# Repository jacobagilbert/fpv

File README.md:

# Custom FPV Related Software and Hardware
This repository contains various FPV related projects. These are side projects for me, and are free for anyone to use under the MIT license. 
I welcome anyone who would like to help and improve on these!

I will attempt to keep this readme up-to-date and provide all resources I have used.

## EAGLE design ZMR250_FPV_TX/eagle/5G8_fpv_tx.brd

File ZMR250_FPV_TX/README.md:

# Custom FPV Transmitter for ZMR250: The ZTX-23

I suggest you read this entire README prior to building this, it's not that long and there are a few important considerations.

### Version 1.2 Changelog:

The version 1.2 hardware has resolved a few issues and annoyances:

- Addition of LDO to resolve SMPS noise in video
- Input connector is now a 5-pin picoblade to distinguish from the programming header
- Changed footprint for 7343 capacitors
- Switch and LED positions are changed for easier access
- Requires modification of the Pololu module

The remainder of this guide is for v1.2 only.

### Origins:

I had a number of annoyances related to the BOSCAM FPV transmitter I initially purchased for my ZRM250 quadcopter. It was difficult to change frequencies, mounting wasn't ideal, and most of all for whatever reason, it only put out 13.1 dBm (~20mW). I knew I was going to need another one, and I happened to stumble across a [German RC forum post](http://fpv-treff.de/viewtopic.php?f=23&t=5974) where an awesome guy developed a custom transmitter based around the TX5823 200mW 5.8GHz transmitter found in many pre-packaged FPV transmitters. While not exactly what I wanted, it was a great starting point and served as the inspiration for this project.

There are a number of differences from the original work, specifically the ATTiny software and PCB layout are completely new, but they get a ton of credit for all the great stuff in that forum .

### Project Objectives:

This project seeks to produce a 200mW FPV transmitter with the following specifications:

- Easily mounted securely on the ZMR250 frame
- Low profile and does not inhibit use of 6" propellers
- Simple to change channels (no buried DIP switches!)
- Direct 3S/4S power input
- Has frequency agility supporting all current receiver channels (including IRC's new 'RaceBand'!)

### Current System Status Overview:

**ATTiny Firmware:** The current ATTiny firmware has been tested on the hardware platform successfully! There are no known issues with the current software. I have used it many times and overall I am quite pleased. All 5 bands (40 channels total) have been implemented.

**Hardware:** The v2.1 boards are in and have been populated and tested - they function great. These were made through OSHPark and can be ordered [here](https://oshpark.com/shared_projects/h9UIDucG) - $12 for 3 copies. There are several optional components, which are detailed in a subsequent section.

The RF path is a properly dimensioned CPWG transmission line, and while just at the length where it begins to matter (and it's FR4 at 5.8 GHz...), I figured it would be fun to do it properly. The trace is 55 mils wide with 9 mil spacing on 1.6 mm FR4, so the line has an impedance of between 49 and 51 ohms depending on the dielectric constant (I assume it's somewhere between 4.3 and 4.6 which should be reasonable).

**Weight:** While reducing weight was not a project objective, 250 racers and their pilots are weight-conscious if not sensitive. I made a few measurements and here is how this transmitter measures up. I was previously using a TS351 in a neat 3D printed holder, but it was pretty heavy:

| Hardware     | Weight   | Comments                                  |
|--------------|----------|-------------------------------------------|
|BOSCAM TS351  |23.7g     |Transmitter only, no mounting hardware     |
|TS5823        |8g        |Transmitter only, no mounting hardware     |
|ZTX-23        |**13.3g** |Includes all mounting and cables!          |
|SMA Extension |7g        |30.7g with BOSCAM and no mounting hardware |

So this transmitter is not the lightest transmitter out there, but considering this includes all material required to securely install the transmitter to the frame, I am very pleased.

**Video Quality:** The ZTX-23 works really great. I tested bypassing the 3.3V LDO and using the Pololu module output directly, and one module looked okay, while the other had significant noise. With the LDO, crystal clear video. At this point I recommend using the LDO (it's ~$0.50) and making the modification to the Pololu module mentioned below.

### Repository Structure:

- eagle/			Eagle PCB files
- attiny/			ATTiny related files and firmware for board
- FPV_TX_BOM.xlsx		Bill of materials to populate boards
- ZMR250_FPV_TX_v1.2.zip	Compressed archive of all gerber files
- README_v1.0.md		Version 1.0 README, out of date but preserved
- README.md			This README

### Bill of Materials:

BOM is up. There are only a handful of components, but the large capacitors are all 7343 size tantalum and the small capacitors are all 0.1uf decoupling caps, the Pololu module is a 500mA 3.3V SMPS, R1 is 330 ohm and R2/R3 are 3.3k. The LDO (U2) is an AP2112 3.3V fixed-output reg. All the small passives are 0805 (however SparkFun's 0805 footprint is a little tight... If you have them, use 0603 for bypass capacitor and resistors).

### Component Modifications:

Both the TX5823 module and Pololu SMPS must be modified before they can be used for this application.

**TX5823 Module Modifications:** It is necessary to modify the TX5823 module so it is able to operate in SPI mode. The modification only require the removal of a single resistor, however it is under the metal shield on the module so you will need to remove that first. This information is available in either the datasheet of the RTC6705 chip.

The easiest way to make the modification is to work one side at a time (they are soldered on two sides) with a soldering iron and precision slotted screwdriver. Use the screwdriver between the module board and shield to *gently* apply pressure while melting the solder. If you work carefully, alternating sides, and taking breaks to allow the module to cool down it is fairly easy to remove the shield. Clean up any excess solder, and remove the resistor shown in the following image:

After removing the resistor, inspect the board (preferrably under a magnifying glass) to ensure you have not accidentally caused any shorts or displaced any other components; replace the shield. This only needs to be done once so you can re-solder the shield to the module PCB.

More information regarding SPI mode operation is available in the limited datasheet, and under the 'attiny' directory.

**Pololu Module Modification:** In order to use the 3.3V LDO, the input must be around 3.6V due to the dropout voltage. This requires a change in the Pololu module, which fortunately is simple - soldering a resistor in parallel with 22.1k R2 on the Pololu module will increase the module output voltage by approximately 350mV and will properly power the LDO. This combination has good efficency on 3S/4S and provides clean power.

The resistor that must be changed by adding another in parallel is shown above, simply solder a ~150k resistor in parallel with it. This value can be deterined from the datasheet for the SMPS controller used, available from Pololu.

### Mounting Transmitter:

One of the design criteria for this transmitter was mounting natively to the ZMR250 frame. Consistant with that, it has been designed to mount cleanly to the rear of the top plate, though the hole in the rear must be drilled out with a 0.25" bit to accomodate the SMA connector. By mounting the SMA connector directly to the frame, it is very unlikely that a crash will damage the transmitter. Be careful drilling carbon fiber as it can be a little tricky, and don't inhale the dust!

On the other end from the SMA connector are two slots that will nicely fit M3 nylon hardware. A spacer is needed to keep some standoff from the conductive frame. I used the smallest diameter HQ propeller mounting bushings since they were a pretty good fit but I'll probably 3D print some spacers that are sized better and post the files when I am happy.

### Connectors:

There are two connectors on the board, a 5 pin Molex PicoBlade PTH connector for power and video input, and a 6 pin PicoBlade PTH connector for programming. I recommend populating only the 5 pin input connector so they are not confused when conecting hardware. To program the microcontroller, I bend the pins slightly on the 6 pin header so they press-fit securely and remove the connector when I am through.

### Transmitter Operation:

The transmitter will remember the last channel used and will automatically configure to this channel on startup. To view the current frequency, you can push the button once quickly and the LED will flash the current band (1-5) followed by a brief pause, followed by the current channel (1-8). To change the frequency, the following procedure should be used:

1. Press and hold the button until the LED turns off and immediately release it. In order to prevent accidental channel changing if you hold it too long, or release it too early it will not set the frequency.
2. The LED will flash quickly and stop. Press the button to set the band (eg: 3 presses will select band 3, "Band E"). If you press the button more than 5 times (the total number of supported bands), it will loop back to 1.
3. Wait for the LED to flash quickly again and set the channel using the same procedure as above. There are 8 channels in each band, and pressing more than 8 times will loop back to 1.
4. Release the button and wait for confirmation that the band has been set (flashes indicating the band, followed by the channel). The transmitter is now reconfigured and will immediately update the frequency of the module, and will start with the new channel in the future.
5. If the button is not pressed to select the band or channel, the frequency selection mode will exit and flash the LED quickly many times. There will be no change to the current or startup channel.

I think I like this scheme but I'm not sure; it might change. Either way, it's a good start that only requires one button and one LED.

### Optional Components:

**Video Input Capacitor:** The TX5823 module specifies a 470uF capacitor on the video input line (C3). These are rather expensive, and I'm not sure it is strictly necessary so I added pads that can be solder-jumpered to bypass the capacitor. I have tested both with and without this cap, and could not see a difference. I will most likely not purchase these again.

**Pololu Module Capacitor:** Pololu recommends the use of a large value capacitor to prevent damage from any turn-on voltage spike. They suggest an input of under 20V with short leads should be fine, but I included the pads anyway. I include them just in case, but like the video input cap, these are fairly expensive. If you do use one, make sure it is rated for the appropriate voltage.

**Audio Grounding Resistor:** I included pads for a resistor (R4) that can be used to terminate the audio input, which is no longer connected to the input connector. Feel free to omit this.

**Noise Reduction Capacitor:** The LDO NR capacitor (C6) should only be used with LDOs that require this. The AP2112 I have in the BOM has this pin as a NC and thus C6 should NOT be populated.

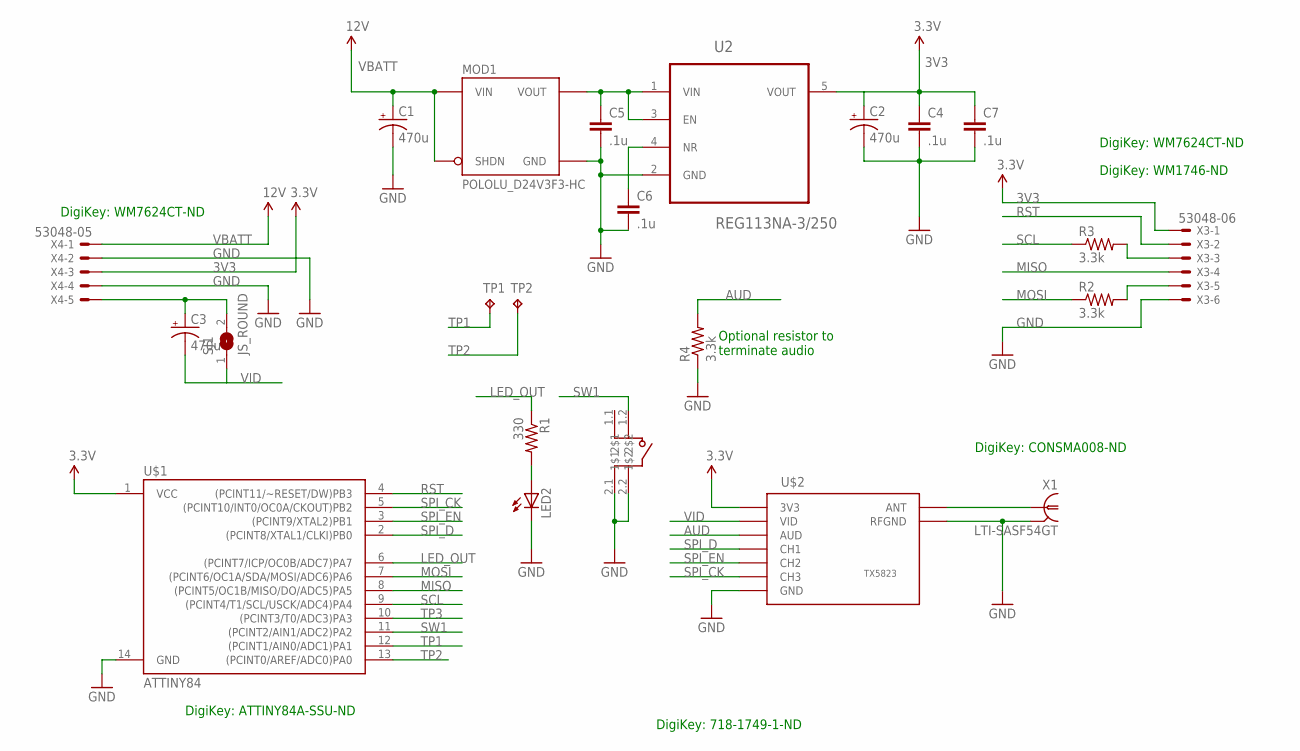
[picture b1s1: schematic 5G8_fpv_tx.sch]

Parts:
C1, C2, C3: 470u; VISHAY_D
C4, C5, C6, C7: .1u; 0805
LED2: LEDCHIPLED_0805; CHIPLED_0805
MOD1: POLOLU_D24V3F3-HC; POLOLU_D24V3F_HC
R1: 330; 0805
R2, R3, R4: 3.3k; 0805
SJ1: JS_ROUND; SJ_ROUND
TP1, TP2: TPTP06SQ; TP06SQ
U2: REG113NA-3/250; SOT95P280X145-5N
U$1: ATTINY84; SO14
U$2: TX5823
U$3: BOURNS_7814G_SW; 7914G
X1: LTI-SASF54GT
X3: 53048-06
X4: 53048-05

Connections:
3V3: C2.+, C4.1, C7.1, U2.5 (VOUT), U$1.1 (VCC), U$2.P$4 (3V3), X3.1, X4.3
ANT: U$2.P$10 (ANT), X1.1
AUD: R4.2, U$2.P$2 (AUD)
GND: C1.-, C2.-, C4.2, C5.2, C6.2, C7.2, LED2.C, MOD1.G (GND), R4.1, U2.2 (GND), U$1.14 (GND), U$2.P$3 (GND), U$2.P$5 (GND), U$2.P$9 (RFGND), U$2.P$11 (RFGND), U$3.2.1 (2$1), U$3.2.2 (2$2), X1.2, X1.3 (2), X1.4 (2), X1.5 (2), X3.6, X4.2, X4.4
LED: LED2.A, R1.2
LED_OUT: R1.1, U$1.6 ((PCINT7/ICP/OC0B/ADC7)PA7)
MISO: U$1.8 ((PCINT5/OC1B/MISO/DO/ADC5)PA5), X3.4
MOSI: R2.1, U$1.7 ((PCINT6/OC1A/SDA/MOSI/ADC6)PA6)
MOSI_: R2.2, X3.5
unnamed: C5.1, MOD1.O (VOUT), U2.1 (VIN), U2.3 (EN)
unnamed: C6.1, U2.4 (NR)
RST: U$1.4 ((PCINT11/~RESET/DW)PB3), X3.2
SCL: R3.1, U$1.9 ((PCINT4/T1/SCL/USCK/ADC4)PA4)
SCL_: R3.2, X3.3
SPI_CK: U$1.5 ((PCINT10/INT0/OC0A/CKOUT)PB2), U$2.P$8 (CH3)
SPI_D: U$1.2 ((PCINT8/XTAL1/CLKI)PB0), U$2.P$6 (CH1)
SPI_EN: U$1.3 ((PCINT9/XTAL2)PB1), U$2.P$7 (CH2)
SW1: U$1.11 ((PCINT2/AIN1/ADC2)PA2), U$3.1.2 (1$2)
TP1: TP1.TP, U$1.12 ((PCINT1/AIN0/ADC1)PA1)
TP2: TP2.TP, U$1.13 ((PCINT0/AREF/ADC0)PA0)
TP3: U$1.10 ((PCINT3/T0/ADC3)PA3)
VBATT: C1.+, MOD1.I (VIN), MOD1.S (SHDN), X4.1
VID: C3.-, SJ1.1, U$2.P$1 (VID)
VID_IN: C3.+, SJ1.2, X4.5

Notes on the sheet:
DigiKey: WM7624CT-ND
DigiKey: ATTINY84A-SSU-ND
DigiKey: CONSMA008-ND
DigiKey: 718-1749-1-ND
DigiKey: WM1746-ND
Optional resistor to terminate audio

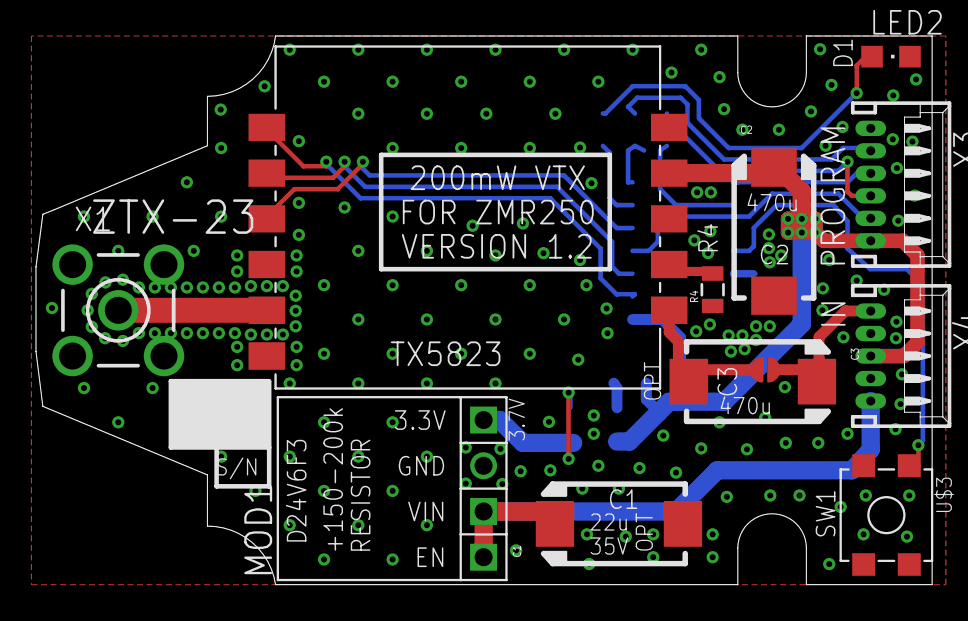
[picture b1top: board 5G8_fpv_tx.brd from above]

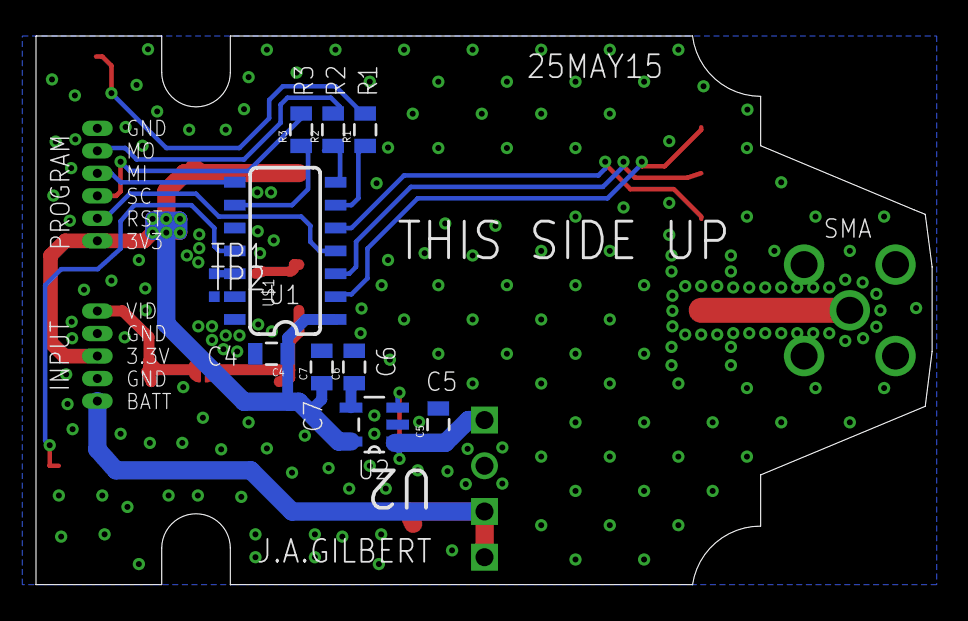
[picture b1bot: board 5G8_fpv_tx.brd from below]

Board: 2 copper layers, 49.8 x 30.5 mm, 23 parts (11 on the bottom side), 23 nets.

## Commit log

2015-04-26 added BOSCAM TX/RX library and updated readme
2015-04-26 readme
2015-04-26 initial commit of ZMR250 transmitter
2015-04-26 added TX/RX module/IC docuemnts
2015-04-29 added attiny source
2015-04-29 updated readme and added pictures of board
2015-04-29 fixed image link
2015-04-29 updated readme....new at the images stuff
2015-04-29 added information about SPI modification to RX5823
2015-04-29 updated images
2015-04-29 moved attiny stuff to new folder, updated READMEs
2015-04-29 updated READMEs
2015-04-30 updated frequency synthesizer register settings and updated READMEs
2015-04-30 various updates to READMEs and images, added channel calculator spreadsheet
2015-05-01 updated attiny software fixing a number of problems
2015-05-01 added mounting information
2015-05-01 updated attiny firmware for more correct SPI operation and better defined button interface
2015-05-01 updated readme to reflect changes
2015-05-01 Optimised tiny code
    Included digitalWriteFast library, to make SPI functions way more
    efficient.
2015-05-01 Optimised ATtiny code
    Used direct portmanipulation instead of digitalWrite
2015-05-01 removed digitalwritefast library
    declutter
2015-05-18 added BoM and updated README to reflect some minor issues
2015-05-19 updated BOM error and added notes on interference testing results
2015-05-22 reduced startup delay from 1000 -> 100 ms
2015-05-22 updated documentation with weight information and some notes on version 2
2015-05-22 updated weight table
2015-06-19 updates for v1.2
2015-06-19 added separate EAGLE directory and updated README and latest board files
2015-06-19 a few updates to the firmware, added a heartbeat and a better scheme for initially setting the frequency
2015-06-19 updated README, edited a few images
2015-06-19 updated BOM
2015-06-19 added information about smps mod
2015-06-19 README update
2015-06-20 added additional images
2015-06-20 added finished pictures
2015-06-20 added preview
2015-06-21 added picture of antenna
2015-06-21 updated readme with more information about the source of the project
2015-06-21 added old uncommitted attiny readme changes

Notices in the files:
parts and their libraries:
SparkFun-DigitalIC: Licensing: Creative Commons ShareAlike 4.0 International - https://creativecommons.org/licenses/by-sa/4.0
